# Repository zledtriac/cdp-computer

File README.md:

# CDP computer
<div align="center">
  
</div>
This computer is based on the CDP1802 CPU, made for practicing and learning 
electronics and programming. The computer is similar to the COSMAC ELF but I 
designed it from scratch. I tried to fully utilize the features of the CPU and 
I hope I was able to implement enough stuff to demonstrate how an old computer
worked back then.

The fully assembled computer has a frontpanel with switches and two row of LEDs.
The first top row indicates the memory address, and then the next row indicates
the data and the control signals. The switches can be used to input data
in the memory and to control the CPU.

## The motherboard
I made the motherboard to be able to run by itself, so for someone who just want
to do some experiments with an old hardware, it is not necessary to build the 
whole computer. The motherboard contains the CPU, RAM, ROM and the clock 
generator.

### The clock generator
The clock runs on 2.4576MHz so if someone want to make a software Serial 
communcation with the Q and EF pins, 9600 baudrate can be achieved with high 
accuracy.

### The memory
The memory is divided into two sections ROM and RAM, but there is an option to
use only RAM for the program too. This is because EPROMs is a bit difficult to
obtain so for those who are just experimenting, the ROM is not necessary to
make the motherboard running, the RAM is enough. If the J5 pins are shorted the
motherboard will only use the RAM, but if those pins are not shorted then the
first 8192 bytes of RAM will be replaced by the ROM. With this feature the
motherboard can handle 64kB of RAM or 8kB of ROM and 56kB of RAM, depending on 
the state of the J5 pins.

### The DMA interface
The board has a DMA interface which can be used to upload programs or snipets of 
data in the memory while the CPU running, or if it is in the LOAD state.

The DMA interface has an 8bit data input port on the J2 pin header, and it has a 
write control signal on the J3 pin header (pin 2.). if there is a rising edge on 
the write pin, a DMA request will be sent to the CPU and the data pesent on the 
J2 pin header will be written in the memory location addressed by the R0 register 
in the CPU.

## The LED driver board
This board is an extension board, to handle the switches and the indicator LEDs. 
Since the CPU can't drive the LEDs directly, it needs a separate board to have 
the necessary ICs to drive the LEDs with relatively high current (5-6mA).

This board contains D-latches and some logic circuits to extend the 8bit address 
bus to 16bit and to generate a selectable 16Hz clock source and a circuit to be 
able to handle the CLEAR, WAIT, and STEP signals.

## The IO board
This board is made to add some input and output capabilities. The board has 3 
parallel input/output which can be configured from software. It is using the 
dedicated IO cotrol of the CPU so it doesn't need any special controlling routine.

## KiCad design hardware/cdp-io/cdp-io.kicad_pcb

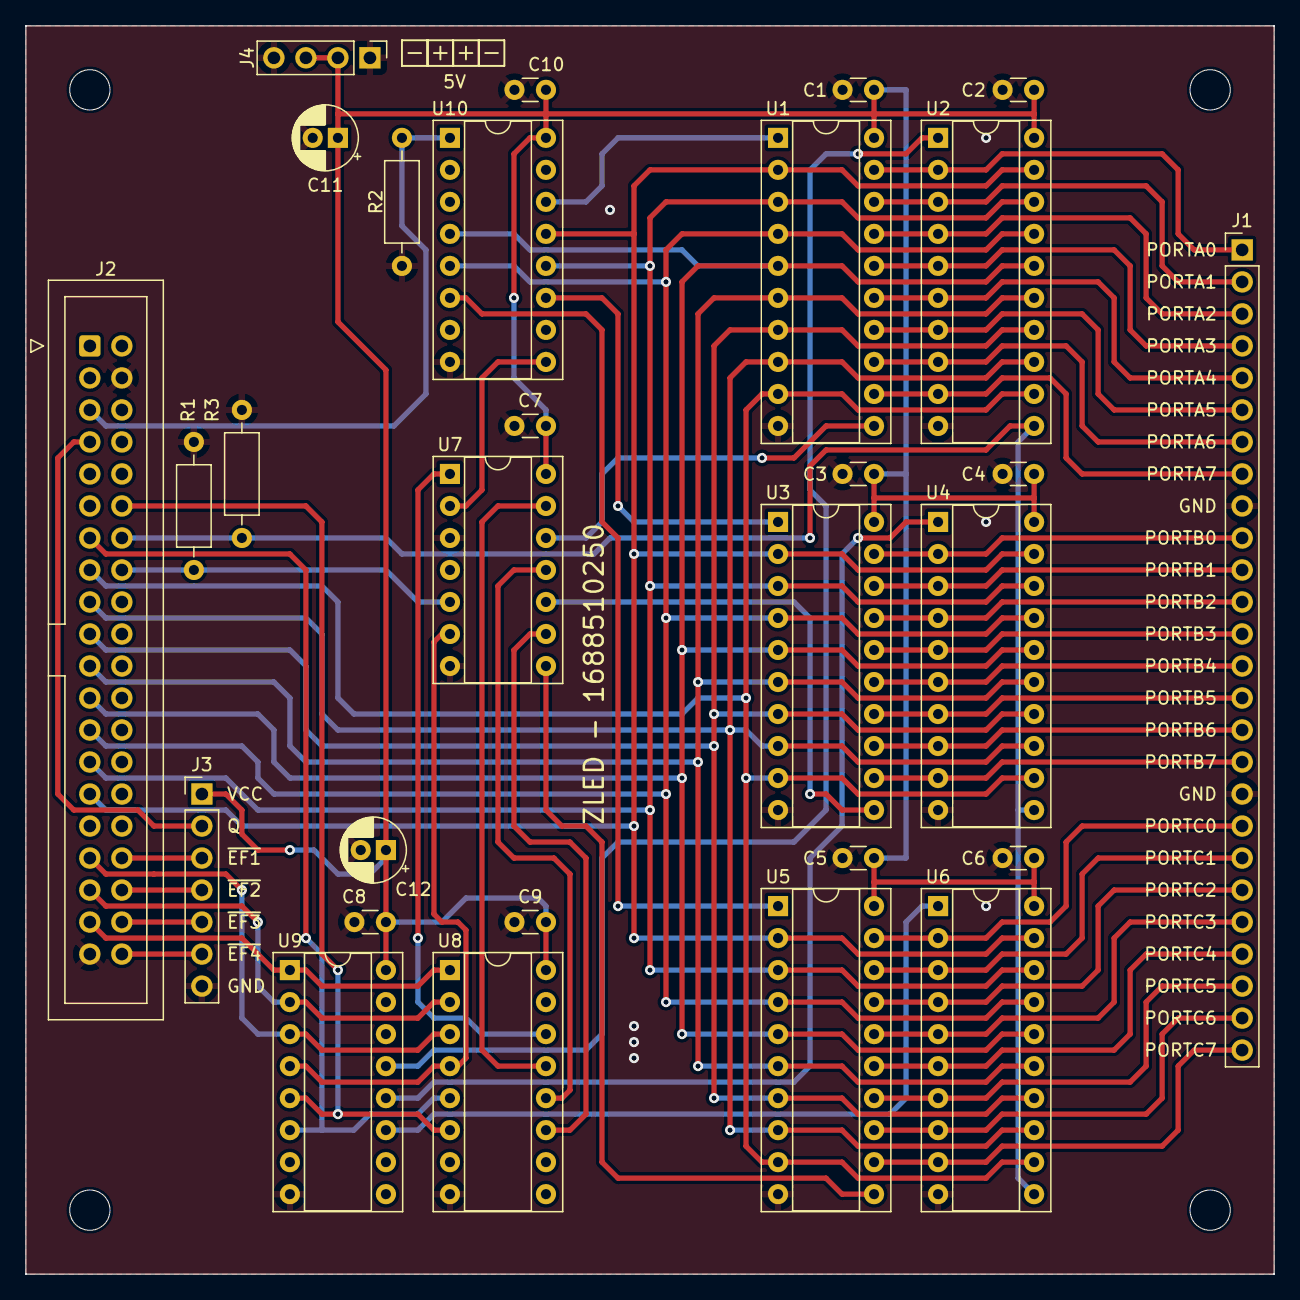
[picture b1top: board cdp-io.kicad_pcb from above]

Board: 2 copper layers, 99.1 x 99.1 mm, 29 parts (0 on the bottom side), 62 nets.

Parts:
C1, C2, C3, C4, C5, C6, C7, C8, C9, C10: 100n; C_Disc_D3.0mm_W1.6mm_P2.50mm
C11, C12: 22uF; CP_Radial_D5.0mm_P2.00mm
J1: Conn_01x26_Pin; PinHeader_1x26_P2.54mm_Vertical
J2: Conn_02x20_Odd_Even; IDC-Header_2x20_P2.54mm_Vertical
J3: Conn_01x07_Pin; PinHeader_1x07_P2.54mm_Vertical
J4: Conn_01x04_Pin; PinHeader_1x04_P2.54mm_Vertical
R1, R2, R3: 47k; R_Axial_DIN0207_L6.3mm_D2.5mm_P10.16mm_Horizontal
U1, U2, U3, U4, U5, U6: 74HC573; DIP-20_W7.62mm_Socket
U7: 74HC14; DIP-14_W7.62mm_Socket
U8, U9: 74HC138; DIP-16_W7.62mm_Socket
U10: 74HC175; DIP-16_W7.62mm_Socket

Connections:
D0: J2.29, U1.2 (D0), U2.19 (Q0), U3.2 (D0), U4.19 (Q0), U5.2 (D0), U6.19 (Q0), U10.13 (D3)
D1: J2.27, U1.3 (D1), U2.18 (Q1), U3.3 (D1), U4.18 (Q1), U5.3 (D1), U6.18 (Q1), U10.12 (D2)
D2: J2.25, U1.4 (D2), U2.17 (Q2), U3.4 (D2), U4.17 (Q2), U5.4 (D2), U6.17 (Q2), U10.5 (D1)
D3: J2.23, U1.5 (D3), U2.16 (Q3), U3.5 (D3), U4.16 (Q3), U5.5 (D3), U6.16 (Q3), U10.4 (D0)
D4: J2.21, U1.6 (D4), U2.15 (Q4), U3.6 (D4), U4.15 (Q4), U5.6 (D4), U6.15 (Q4)
D5: J2.19, U1.7 (D5), U2.14 (Q5), U3.7 (D5), U4.14 (Q5), U5.7 (D5), U6.14 (Q5)
D6: J2.17, U1.8 (D6), U2.13 (Q6), U3.8 (D6), U4.13 (Q6), U5.8 (D6), U6.13 (Q6)
D7: J2.15, U1.9 (D7), U2.12 (Q7), U3.9 (D7), U4.12 (Q7), U5.9 (D7), U6.12 (Q7)
GND: C1.2, C2.2, C3.2, C4.2, C5.2, C6.2, C7.2, C8.2, C9.2, C10.2, C11.2, C12.2, J1.9, J1.18, J2.4, J2.39, J3.7, J4.1, J4.4, R1.2, R2.2, R3.2, U1.10 (GND), U2.10 (GND), U3.10 (GND), U4.10 (GND), U5.10 (GND), U6.10 (GND), U7.3, U7.7 (GND), U8.8 (GND), U9.8 (GND), U10.8 (GND)
N0: J2.37, U8.1 (A0), U9.1 (A0)
N1: J2.35, U8.2 (A1), U9.2 (A1)
N2: J2.33, U8.3 (A2), U9.3 (A2)
unnamed: U1.11 (Load), U7.12
unnamed: U3.11 (Load), U7.10
unnamed: U5.11 (Load), U7.8
unnamed: U7.6, U8.4 (E1), U9.4 (E1)
unnamed: U7.2, U10.9 (Cp)
PORTA0: J1.1, U1.19 (Q0), U2.2 (D0)
PORTA1: J1.2, U1.18 (Q1), U2.3 (D1)
PORTA2: J1.3, U1.17 (Q2), U2.4 (D2)
PORTA3: J1.4, U1.16 (Q3), U2.5 (D3)
PORTA4: J1.5, U1.15 (Q4), U2.6 (D4)
PORTA5: J1.6, U1.14 (Q5), U2.7 (D5)
PORTA6: J1.7, U1.13 (Q6), U2.8 (D6)
PORTA7: J1.8, U1.12 (Q7), U2.9 (D7)
PORTB0: J1.10, U3.19 (Q0), U4.2 (D0)
PORTB1: J1.11, U3.18 (Q1), U4.3 (D1)
PORTB2: J1.12, U3.17 (Q2), U4.4 (D2)
PORTB3: J1.13, U3.16 (Q3), U4.5 (D3)
PORTB4: J1.14, U3.15 (Q4), U4.6 (D4)
PORTB5: J1.15, U3.14 (Q5), U4.7 (D5)
PORTB6: J1.16, U3.13 (Q6), U4.8 (D6)
PORTB7: J1.17, U3.12 (Q7), U4.9 (D7)
PORTC0: J1.19, U5.19 (Q0), U6.2 (D0)
PORTC1: J1.20, U5.18 (Q1), U6.3 (D1)
PORTC2: J1.21, U5.17 (Q2), U6.4 (D2)
PORTC3: J1.22, U5.16 (Q3), U6.5 (D3)
PORTC4: J1.23, U5.15 (Q4), U6.6 (D4)
PORTC5: J1.24, U5.14 (Q5), U6.7 (D5)
PORTC6: J1.25, U5.13 (Q6), U6.8 (D6)
PORTC7: J1.26, U5.12 (Q7), U6.9 (D7)
Q: J2.7, J3.2
TPA: J2.14, R3.1, U2.11 (Load), U4.11 (Load), U6.11 (Load)
TPB: J2.16, R1.1, U7.5
VCC: C1.1, C2.1, C3.1, C4.1, C5.1, C6.1, C7.1, C8.1, C9.1, C10.1, C11.1, C12.1, J3.1, J4.2, J4.3, U1.20 (VCC), U2.20 (VCC), U3.20 (VCC), U4.20 (VCC), U5.20 (VCC), U6.20 (VCC), U7.14 (VCC), U8.16 (VCC), U9.16 (VCC), U10.16 (VCC)
~CLEAR: J2.5, R2.1, U10.1 (~Mr)
~CTRL WRITE: U7.1, U8.14 (O1)
~EF1: J2.34, J3.3
~EF2: J2.36, J3.4
~EF3: J2.38, J3.5
~EF4: J2.40, J3.6
~MRD: J2.13, U8.5 (E2), U9.6 (E3)
~MWR: J2.12, U8.6 (E3), U9.5 (E2)
~PORTA OUTPUT: U1.1 (OE), U10.14 (~Q3)
~PORTA READ: U2.1 (OE), U9.13 (O2)
~PORTA WRITE: U7.13, U8.13 (O2)
~PORTB OUTPUT: U3.1 (OE), U10.11 (~Q2)
~PORTB READ: U4.1 (OE), U9.12 (O3)
~PORTB WRITE: U7.11, U8.12 (O3)
~PORTC OUTPUT: U5.1 (OE), U10.6 (~Q1)
~PORTC READ: U6.1 (OE), U9.11 (O4)
~PORTC WRITE: U7.9, U8.11 (O4)

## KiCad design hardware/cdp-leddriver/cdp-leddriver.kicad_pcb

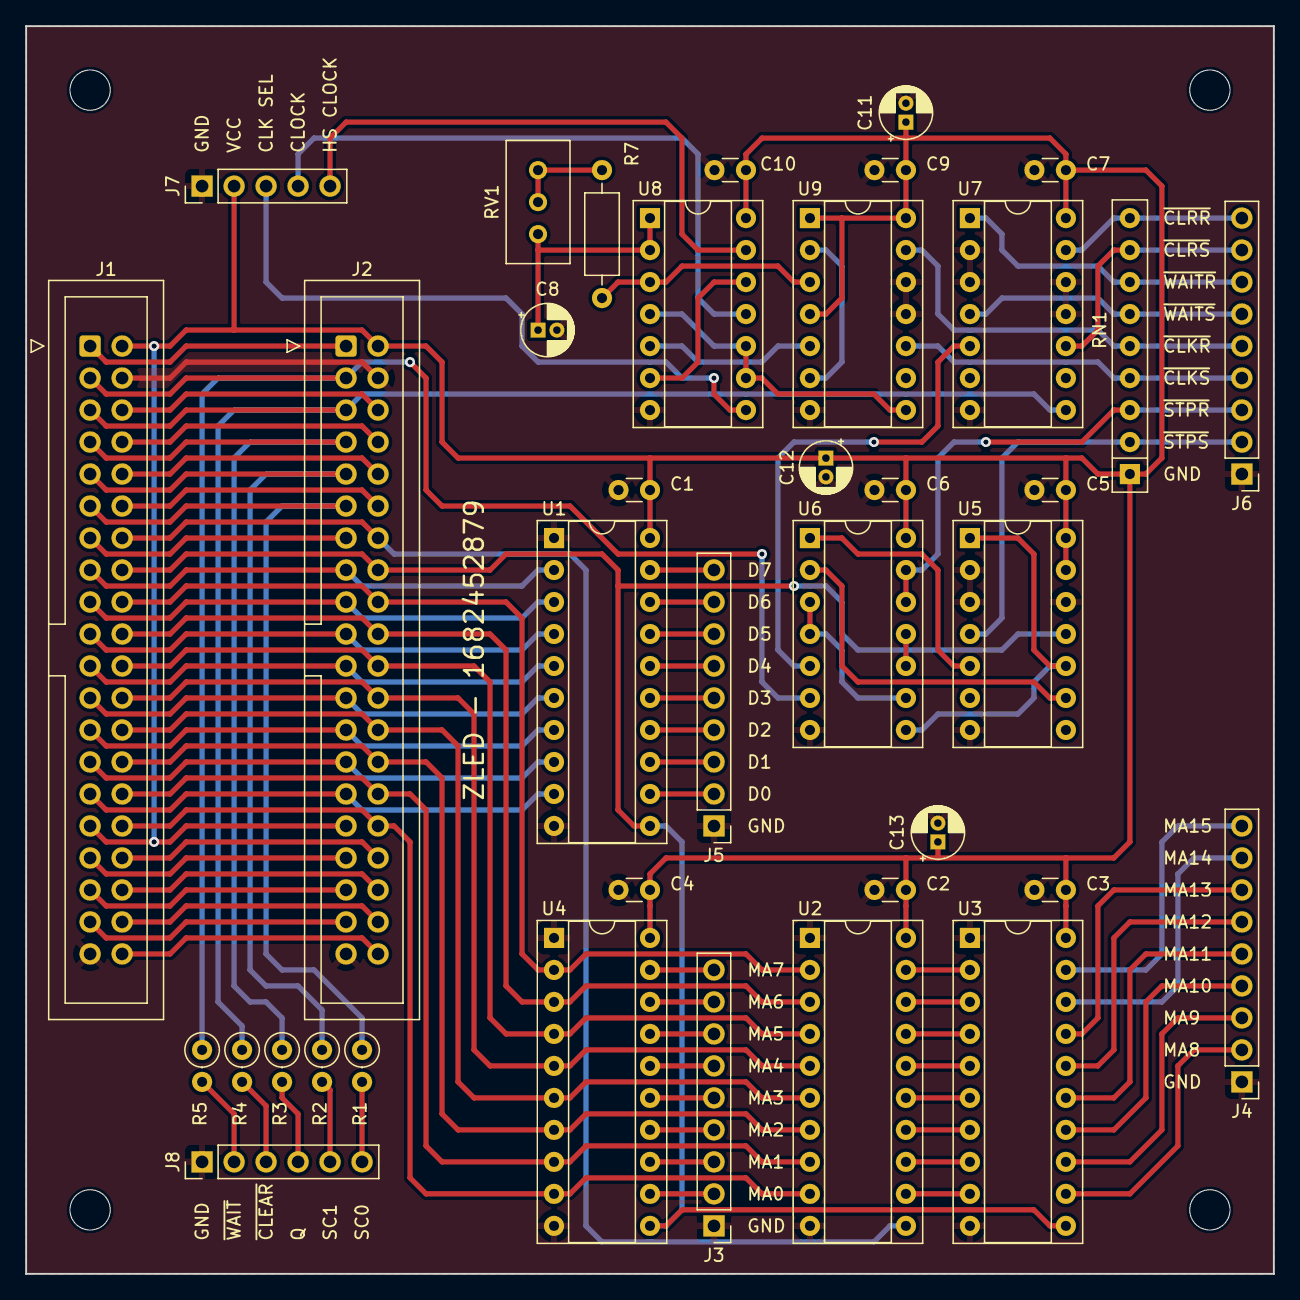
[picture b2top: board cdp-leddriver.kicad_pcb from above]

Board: 2 copper layers, 99.1 x 99.1 mm, 38 parts (0 on the bottom side), 99 nets.

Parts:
C1, C2, C3, C4, C5, C6, C7, C9, C10: 100nF; C_Disc_D3.0mm_W1.6mm_P2.50mm
C8: 1uF; CP_Radial_D4.0mm_P1.50mm
C11, C12, C13: 22uF; CP_Radial_D4.0mm_P1.50mm
J1, J2: Conn_02x20_Odd_Even; IDC-Header_2x20_P2.54mm_Vertical
J3, J4, J5, J6: Conn_01x09_Pin; PinHeader_1x09_P2.54mm_Vertical
J7: Conn_01x05_Pin; PinHeader_1x05_P2.54mm_Vertical
J8: Conn_01x06_Pin; PinHeader_1x06_P2.54mm_Vertical
R1, R2, R3, R4, R5: 1k; R_Axial_DIN0207_L6.3mm_D2.5mm_P2.54mm_Vertical
R7: 4k7; R_Axial_DIN0207_L6.3mm_D2.5mm_P10.16mm_Horizontal
RN1: 10k; R_Array_SIP9
RV1: 10k; Potentiometer_Bourns_3296W_Vertical
U1, U3, U4: 74HC574; DIP-20_W7.62mm_Socket
U2: 74HC573; DIP-20_W7.62mm_Socket
U5, U7, U9: 74HC74; DIP-14_W7.62mm_Socket
U6, U8: 74HC132; DIP-14_W7.62mm_Socket

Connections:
AOUT0: J3.2, U4.12 (Q7)
AOUT1: J3.3, U4.13 (Q6)
AOUT2: J3.4, U4.14 (Q5)
AOUT3: J3.5, U4.15 (Q4)
AOUT4: J3.6, U4.16 (Q3)
AOUT5: J3.7, U4.17 (Q2)
AOUT6: J3.8, U4.18 (Q1)
AOUT7: J3.9, U4.19 (Q0)
AOUT8: J4.2, U3.12 (Q7)
AOUT9: J4.3, U3.13 (Q6)
AOUT10: J4.4, U3.14 (Q5)
AOUT11: J4.5, U3.15 (Q4)
AOUT12: J4.6, U3.16 (Q3)
AOUT13: J4.7, U3.17 (Q2)
AOUT14: J4.8, U3.18 (Q1)
AOUT15: J4.9, U3.19 (Q0)
CLK OUT: J7.4, U8.11
CLK SEL: J7.3, U8.8
CLOCK: J1.1, J2.1
D0: J1.29, J2.29, U1.9 (D7)
D1: J1.27, J2.27, U1.8 (D6)
D2: J1.25, J2.25, U1.7 (D5)
D3: J1.23, J2.23, U1.6 (D4)
D4: J1.21, J2.21, U1.5 (D3)
D5: J1.19, J2.19, U1.4 (D2)
D6: J1.17, J2.17, U1.3 (D1)
D7: J1.15, J2.15, U1.2 (D0)
DOUT0: J5.2, U1.12 (Q7)
DOUT1: J5.3, U1.13 (Q6)
DOUT2: J5.4, U1.14 (Q5)
DOUT3: J5.5, U1.15 (Q4)
DOUT4: J5.6, U1.16 (Q3)
DOUT5: J5.7, U1.17 (Q2)
DOUT6: J5.8, U1.18 (Q1)
DOUT7: J5.9, U1.19 (Q0)
GND: C1.2, C2.2, C3.2, C4.2, C5.2, C6.2, C7.2, C8.2, C9.2, C10.2, C11.2, C12.2, C13.2, J1.4, J1.39, J2.4, J2.39, J3.1, J4.1, J5.1, J6.1, J7.1, J8.1, U1.1 (OE), U1.10 (GND), U2.1 (OE), U2.10 (GND), U3.1 (OE), U3.10 (GND), U4.1 (OE), U4.10 (GND), U5.2 (D), U5.3 (C), U5.7 (GND), U5.12 (D), U6.7 (GND), U7.2 (D), U7.3 (C), U7.7 (GND), U7.11 (C), U7.12 (D), U8.7 (GND), U9.7 (GND), U9.11 (C), U9.12 (D)
HS CLK: J7.5, U8.13
MA0: J1.32, J2.32, U2.9 (D7), U4.9 (D7)
MA1: J1.30, J2.30, U2.8 (D6), U4.8 (D6)
MA2: J1.28, J2.28, U2.7 (D5), U4.7 (D5)
MA3: J1.26, J2.26, U2.6 (D4), U4.6 (D4)
MA4: J1.24, J2.24, U2.5 (D3), U4.5 (D3)
MA5: J1.22, J2.22, U2.4 (D2), U4.4 (D2)
MA6: J1.20, J2.20, U2.3 (D1), U4.3 (D1)
MA7: J1.18, J2.18, U2.2 (D0), U4.2 (D0)
N0: J1.37, J2.37
N1: J1.35, J2.35
N2: J1.33, J2.33
unnamed: C8.1, RV1.3, U8.1, U8.2
unnamed: J8.2, R5.2
unnamed: J8.3, R4.2
unnamed: J8.4, R3.2
unnamed: J8.5, R2.2
unnamed: J8.6, R1.2
unnamed: R7.1, RV1.1, RV1.2
unnamed: U2.19 (Q0), U3.2 (D0)
unnamed: U2.18 (Q1), U3.3 (D1)
unnamed: U2.17 (Q2), U3.4 (D2)
unnamed: U2.16 (Q3), U3.5 (D3)
unnamed: U2.15 (Q4), U3.6 (D4)
unnamed: U2.14 (Q5), U3.7 (D5)
unnamed: U2.13 (Q6), U3.8 (D6)
unnamed: U2.12 (Q7), U3.9 (D7)
unnamed: U5.5 (Q), U6.1
unnamed: U5.1 (~R), U5.10 (~S), U6.8
unnamed: U5.9 (Q), U6.2
unnamed: U6.3, U6.4, U6.9
unnamed: U6.10, U6.11
unnamed: U6.5, U7.5 (Q)
unnamed: U8.6, U8.12
unnamed: R7.2, U8.3, U9.3 (C)
unnamed: U9.2 (D), U9.6 (~Q)
unnamed: U8.5, U9.5 (Q)
unnamed: U8.4, U8.9, U8.10, U9.8 (~Q)
Q: J1.7, J2.7, R3.1
SC0: J1.11, J2.11, R1.1
SC1: J1.9, J2.9, R2.1
TPA: J1.14, J2.14, U2.11 (Load)
TPB: J1.16, J2.16, U1.11 (Cp), U3.11 (Cp), U4.11 (Cp), U5.11 (C)
VCC: C1.1, C2.1, C3.1, C4.1, C5.1, C6.1, C7.1, C9.1, C10.1, C11.1, C12.1, C13.1, J1.2, J1.31, J2.2, J2.31, J7.2, RN1.1 (common), U1.20 (VCC), U2.20 (VCC), U3.20 (VCC), U4.20 (VCC), U5.13 (~R), U5.14 (VCC), U6.14 (VCC), U7.14 (VCC), U8.14 (VCC), U9.1 (~R), U9.4 (~S), U9.14 (VCC)
~CLEAR RESET: J6.9, RN1.9 (R8), U7.13 (~R)
~CLEAR SET: J6.8, RN1.8 (R7), U7.10 (~S)
~CLEAR: J1.5, J2.5, R4.1, U7.8 (~Q)
~CLOCK RESET: J6.5, RN1.5 (R4), U9.13 (~R)
~CLOCK SET: J6.4, RN1.4 (R3), U9.10 (~S)
~DMA IN: J1.6, J2.6
~DMA OUT: J1.8, J2.8
~EF1: J1.34, J2.34
~EF2: J1.36, J2.36
~EF3: J1.38, J2.38
~EF4: J1.40, J2.40
~INTERRUPT: J1.10, J2.10
~MRD: J1.13, J2.13
~MWR: J1.12, J2.12
~STEP RESET: J6.3, RN1.3 (R2), U6.12, U6.13
~STEP SET: J6.2, RN1.2 (R1), U5.4 (~S)
~WAIT RESET: J6.7, RN1.7 (R6), U7.1 (~R)
~WAIT SET: J6.6, RN1.6 (R5), U7.4 (~S)
~WAIT: J1.3, J2.3, R5.1, U6.6

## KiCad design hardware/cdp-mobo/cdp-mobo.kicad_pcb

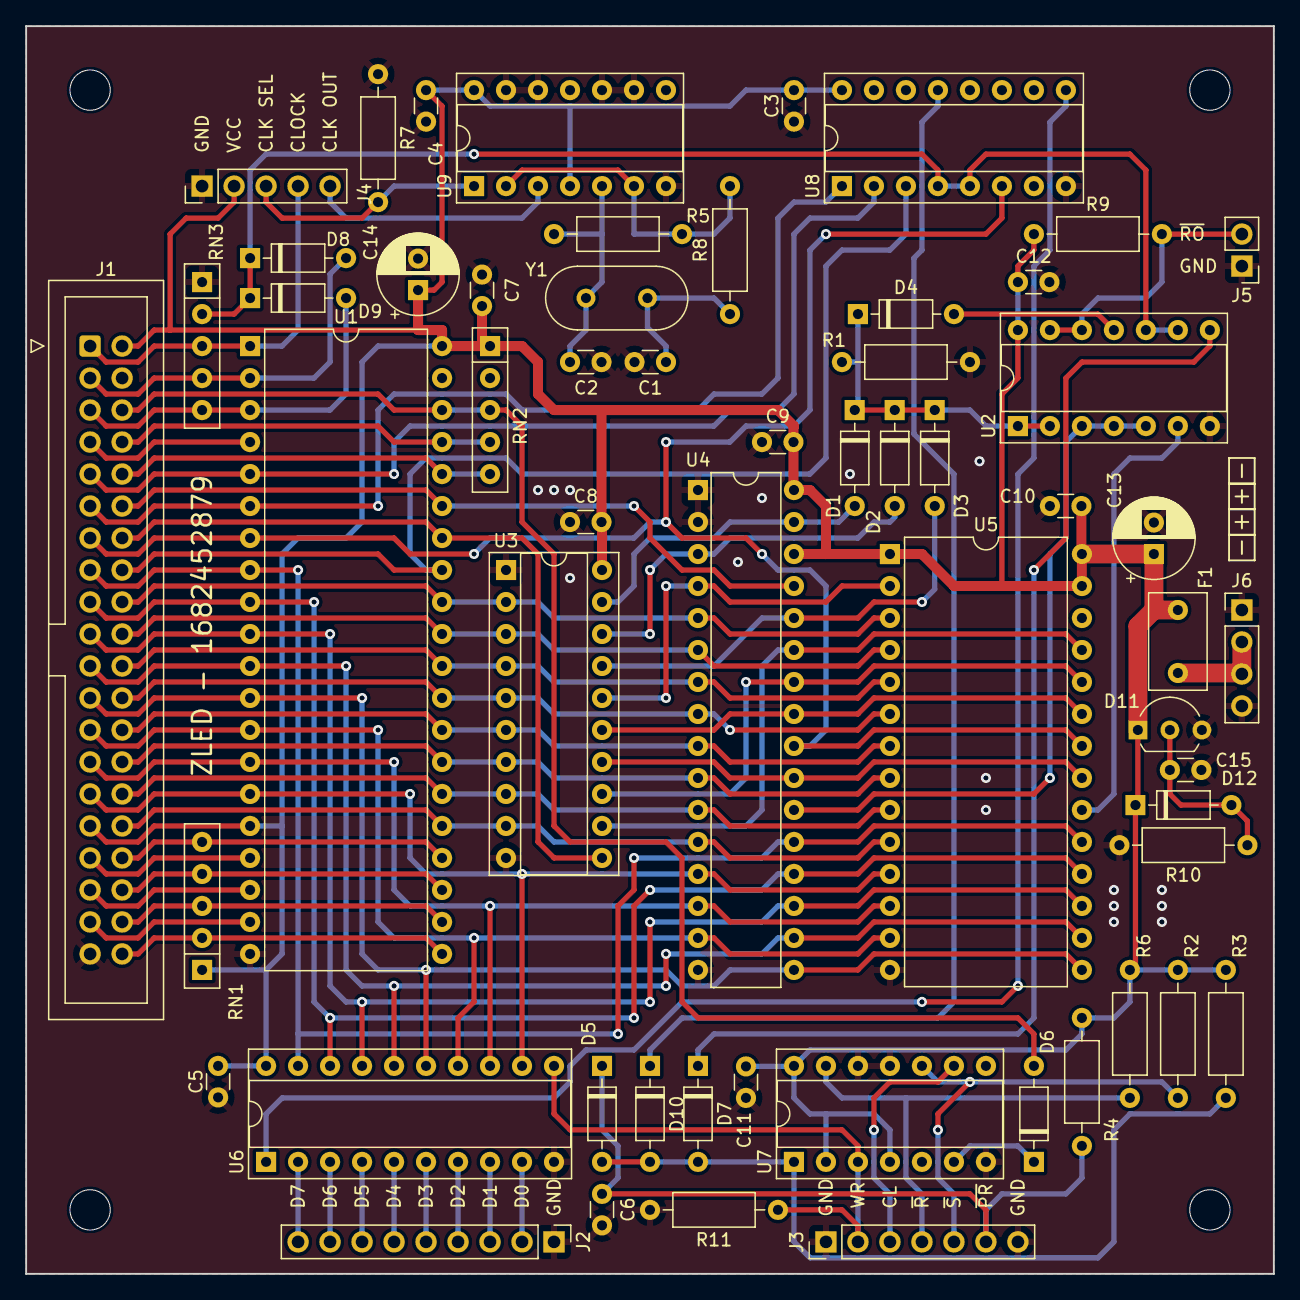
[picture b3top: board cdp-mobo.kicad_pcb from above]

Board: 2 copper layers, 99.1 x 99.1 mm, 58 parts (0 on the bottom side), 77 nets.

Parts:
C1, C2: 22pF; C_Disc_D3.0mm_W1.6mm_P2.50mm
C3, C4, C5, C7, C8, C9, C10, C11, C12, C15: 100nF; C_Disc_D3.0mm_W1.6mm_P2.50mm
C6: 220nF; C_Disc_D3.0mm_W1.6mm_P2.50mm
C13, C14: 100uF; CP_Radial_D6.3mm_P2.50mm
D1, D2, D3, D4, D5, D6, D7, D8, D9, D10: 1N4148; D_DO-35_SOD27_P7.62mm_Horizontal
D11: BT149D; TO-92L_Inline_Wide
D12: BZX55C5V1; D_DO-35_SOD27_P7.62mm_Horizontal
F1: 400mA; C_Disc_D7.5mm_W4.4mm_P5.00mm
J1: Conn_02x20_Odd_Even; IDC-Header_2x20_P2.54mm_Vertical
J2: Conn_01x09_Pin; PinHeader_1x09_P2.54mm_Vertical
J3: Conn_01x07_Pin; PinHeader_1x07_P2.54mm_Vertical
J4: Conn_01x05_Pin; PinHeader_1x05_P2.54mm_Vertical
J5: Conn_01x02_Pin; PinHeader_1x02_P2.54mm_Vertical
J6: Conn_01x04_Pin; PinHeader_1x04_P2.54mm_Vertical
R1, R2, R6, R7, R9, R11: 10k; R_Axial_DIN0207_L6.3mm_D2.5mm_P10.16mm_Horizontal
R3, R4: 20k; R_Axial_DIN0207_L6.3mm_D2.5mm_P10.16mm_Horizontal
R5: 1M; R_Axial_DIN0207_L6.3mm_D2.5mm_P10.16mm_Horizontal
R8, R10: 1k; R_Axial_DIN0207_L6.3mm_D2.5mm_P10.16mm_Horizontal
RN1, RN2, RN3: R_Network04; R_Array_SIP5
U1: CDP1802ACE; DIP-40_W15.24mm
U2: 74HC132; DIP-14_W7.62mm_Socket
U3: 74HC573; DIP-20_W7.62mm_Socket
U4: W24512AK-20; DIP-32_W7.62mm
U5: 2764; DIP-28_W15.24mm
U6: 74HC574; DIP-20_W7.62mm_Socket
U7: 74HC74; DIP-14_W7.62mm_Socket
U8: 74HC138; DIP-16_W7.62mm_Socket
U9: 74HC00; DIP-14_W7.62mm_Socket
Y1: 2MHz; Crystal_HC49-U_Vertical

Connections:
/CPU and memories/MA8: U3.12 (Q7), U4.27 (A8), U5.25 (A8)
/CPU and memories/MA9: U3.13 (Q6), U4.26 (A9), U5.24 (A9)
/CPU and memories/MA10: U3.14 (Q5), U4.23 (A10), U5.21 (A10)
/CPU and memories/MA11: U3.15 (Q4), U4.25 (A11), U5.23 (A11)
/CPU and memories/MA12: U3.16 (Q3), U4.4 (A12), U5.2 (A12)
/CPU and memories/MA13: D3.2 (A), U3.17 (Q2), U4.28 (A13)
/CPU and memories/MA14: D2.2 (A), U3.18 (Q1), U4.3 (A14)
/CPU and memories/MA15: D1.2 (A), U3.19 (Q0), U4.31 (A15)
CLK OUT: J4.5, U9.3
CLK SEL: J4.3, R7.2, U9.1
CLOCK: J1.1, J4.4, RN3.3 (R2), U1.1 (CLOCK)
D0: J1.29, U1.15 (BUS0), U4.13 (D0), U5.11 (D0), U6.12 (Q7)
D1: J1.27, U1.14 (BUS1), U4.14 (D1), U5.12 (D1), U6.13 (Q6)
D2: J1.25, U1.13 (BUS2), U4.15 (D2), U5.13 (D2), U6.14 (Q5)
D3: J1.23, U1.12 (BUS3), U4.17 (D3), U5.15 (D3), U6.15 (Q4)
D4: J1.21, U1.11 (BUS4), U4.18 (D4), U5.16 (D4), U6.16 (Q3)
D5: J1.19, U1.10 (BUS5), U4.19 (D5), U5.17 (D5), U6.17 (Q2)
D6: J1.17, U1.9 (BUS6), U4.20 (D6), U5.18 (D6), U6.18 (Q1)
D7: J1.15, U1.8 (BUS7), U4.21 (D7), U5.19 (D7), U6.19 (Q0)
DIN0: J2.2, U6.9 (D7)
DIN1: J2.3, U6.8 (D6)
DIN2: J2.4, U6.7 (D5)
DIN3: J2.5, U6.6 (D4)
DIN4: J2.6, U6.5 (D3)
DIN5: J2.7, U6.4 (D2)
DIN6: J2.8, U6.3 (D1)
DIN7: J2.9, U6.2 (D0)
DMA WRITE: J3.2, R11.1, U6.11 (Cp), U7.3 (C)
GND: C1.2, C2.2, C3.2, C4.2, C5.2, C6.2, C7.2, C8.1, C9.1, C10.1, C11.1, C12.2, C13.2, C14.2, C15.2, D11.3 (K), J1.4, J1.39, J2.1, J3.1, J3.7, J4.1, J5.1, J6.1, J6.4, R1.2, R7.1, R10.2, R11.2, RN3.1 (common), U1.20 (VSS), U2.7 (GND), U3.1 (OE), U3.10 (GND), U4.1 (NC), U4.2 (NC), U4.16 (VSS), U5.14 (GND), U6.10 (GND), U7.7 (GND), U7.11 (C), U7.12 (D), U8.8 (GND), U9.7 (GND), U9.9, U9.10, U9.12, U9.13
MA0: J1.32, U1.25 (MA0), U3.9 (D7), U4.12 (A0), U5.10 (A0)
MA1: J1.30, U1.26 (MA1), U3.8 (D6), U4.11 (A1), U5.9 (A1)
MA2: J1.28, U1.27 (MA2), U3.7 (D5), U4.10 (A2), U5.8 (A2)
MA3: J1.26, U1.28 (MA3), U3.6 (D4), U4.9 (A3), U5.7 (A3)
MA4: J1.24, U1.29 (MA4), U3.5 (D3), U4.8 (A4), U5.6 (A4)
MA5: J1.22, U1.30 (MA5), U3.4 (D2), U4.7 (A5), U5.5 (A5)
MA6: J1.20, U1.31 (MA6), U3.3 (D1), U4.6 (A6), U5.4 (A6)
MA7: J1.18, U1.32 (MA7), U3.2 (D0), U4.5 (A7), U5.3 (A7)
N0: J1.37, U1.19 (N0)
N1: J1.35, U1.18 (N1)
N2: J1.33, U1.17 (N2)
unnamed: C1.1, R8.1, Y1.2
unnamed: C2.1, R5.2, U9.5, Y1.1
unnamed: D1.1 (K), D2.1 (K), D3.1 (K), D4.1 (K), R1.1, U2.1, U2.2
unnamed: D4.2 (A), U2.11
unnamed: D6.1 (K), U7.6 (~Q)
unnamed: D7.1 (K), U2.8
unnamed: D5.2 (A), D7.2 (A), D10.2 (A), R3.2, U7.1 (~R)
unnamed: D10.1 (K), U8.13 (O2)
unnamed: C15.1, D11.2 (G), D12.2 (A), R10.1
unnamed: F1.2, J6.2, J6.3
unnamed: R5.1, R8.2, U9.2, U9.6
unnamed: U6.1 (OE), U8.9 (O6)
Q: J1.7, U1.4 (Q)
SC0: J1.11, U1.6 (SC0), U8.1 (A0)
SC1: J1.9, U1.5 (SC1), U8.2 (A1)
TPA: J1.14, U1.34 (TPA), U3.11 (Load)
TPB: J1.16, U1.33 (TPB), U8.3 (A2)
VCC: C3.1, C4.1, C5.1, C7.1, C8.2, C9.2, C10.2, C11.2, C12.1, C13.1, C14.1, D11.1 (A), D12.1 (K), F1.1, J1.2, J1.31, J4.2, R2.1, R3.1, R4.1, R6.1, R9.1, RN1.1 (common), RN2.1 (common), U1.16 (VCC), U1.40 (VDD), U2.14 (VCC), U3.20 (VCC), U4.30 (CS2), U4.32 (VDD), U5.1 (VPP), U5.27 (~PGM), U5.28 (VCC), U6.20 (VCC), U7.2 (D), U7.4 (~S), U7.14 (VCC), U8.16 (VCC), U9.4, U9.14 (VCC)
WRITE CLK: J3.3, U7.9 (Q)
~CLEAR: D9.2 (A), J1.5, RN3.5 (R4), U1.3 (~CLEAR)
~DMA IN: D6.2 (A), J1.6, RN2.3 (R2), U1.38 (~DMA_IN)
~DMA OUT: J1.8, RN2.4 (R3), U1.37 (~DMA_OUT)
~EF1: J1.34, RN1.5 (R4), U1.24 (~EF1)
~EF2: J1.36, RN1.4 (R3), U1.23 (~EF2)
~EF3: J1.38, RN1.3 (R2), U1.22 (~EF3)
~EF4: J1.40, RN1.2 (R1), U1.21 (~EF4)
~INTERRUPT: J1.10, RN2.5 (R4), U1.36 (~INTERRUPT)
~LOAD EN: D8.1 (K), D9.1 (K), RN3.2 (R1), U2.9, U2.10, U8.4 (E1), U8.5 (E2)
~MRD: J1.13, U1.7 (~MRD), U4.24 (~OE), U5.22 (~OE), U8.6 (E3)
~MWR: J1.12, U1.35 (~MWR), U4.29 (~WE)
~PROTECT: C6.1, D5.1 (K), J3.6, R4.2
~RAM ONLY: J5.2, R9.2, U2.12, U2.13
~RAM_CS: U2.3, U2.4, U2.5, U4.22 (~CS1)
~ROM_CS: U2.6, U5.20 (~CE)
~WAIT: D8.2 (A), J1.3, RN3.4 (R3), U1.2 (~WAIT)
~WRITE RESET: J3.4, R6.2, U7.13 (~R)
~WRITE SET: J3.5, R2.2, U7.10 (~S)

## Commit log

2023-04-25 Upload files.
2023-05-29 Minor changes in component values, and added a the IO module.
2023-05-29 Added the controller page, and two decoders are placed in it. Moved some files, and added the gitignore file.
2023-06-04 The controller is finished. U7 is changed to a hex inverter.
2023-06-04 Changed the layout a bit, started to work on the PCB.
2023-06-17 Changed the schematic a bit.
2023-07-02 A really small progress.
2023-07-04 Renamed a few net, and changed the schematic a bit. The PCB is ready!
2023-07-06 The final version of the IO board. Gerber files added.
2023-07-06 IC names fixed on the led driver schematic, on the PCB the MA8-MA15 labels were misaligned that is also fixed. Updated the gerber files.
2023-07-06 IC names fixed. PCB is updated. Gerber files are still ok.
2023-07-06 cdpcmobo ZIP file is removed from the gerber folder. Added PDF schematic.
2023-07-21 Added a terminal program.
2023-08-13 Added backspace handling, and 255 character limit to the readline function, and fixed some branches.
2023-09-17 README updated.
2023-10-03 Added a command interpreter, and a hex viewer for analysing the contents of the memory.
2023-10-10 Fixed the parenthesis handling in the interpreter.
2023-10-12 mem_view command now accepts two parameter, fixed some bugs.
2023-10-18 Added HEX parsing so now the terminal can parse hexadecimal numbers.
2023-10-26 Dynamic memory handling is implemented. Commands: mem_debug, mem_alloc <size>, mem_free <address>
2023-10-29 GET_STRING function implemented.
2023-10-30 Saving local registers in DYN_MEMORY_ALLOC.
2023-10-30 Making the GET_STRING call in the LET_STATEMENT for testing.
2023-11-03 LET_STATEMENT is implemented, but needs to be tested.
2023-11-05 variable list init (VAR_LIST_INIT) added.
2023-11-05 mem_alloc size equality test fixed.
2023-11-05 Fixed the addressing in the LET_STATEMENT_FREENODE.
2023-11-09 variable searching is ready to test.
2023-11-09 READ_VAR added to the FACTOR function.
2023-11-10 Minor fix in the READ_VAR.
2023-11-11 READ_VAR fixed.
2023-11-16 Variable handling is working. STATEMENT function is added.
2023-11-16 READ_VAR refactored. Now it is using static memory for storing the variable name.
2023-11-18 Changed the welcome message, and removed the COMMAND_CHECK.
2023-11-19 DMA_SET is working.
2023-11-19 MEM_SET and MEM_WRITE has been added and working.
2023-11-19 EXEC has been added and working.
2024-01-15 Added line operations but not finished.
2024-01-15 Changed the serial input pin.
2024-02-03 Read/Write io operations are added and working.
2024-02-10 SPI operations added.
2024-02-12 SPI communication refactored.
2024-10-03 Upload a picture of the computer.
2024-10-03 Added image to the README.
2025-10-25 Started documenting.
2025-10-25 Function call doc.
